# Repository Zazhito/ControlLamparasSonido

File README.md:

# ControlLamparasSonido
 Controlador de intensidad luminica utilizando sonido , Este proyecto fue extraido del libro "500 ELECTRONIC PROJECTS" del autor ARSATH NATHEEM S

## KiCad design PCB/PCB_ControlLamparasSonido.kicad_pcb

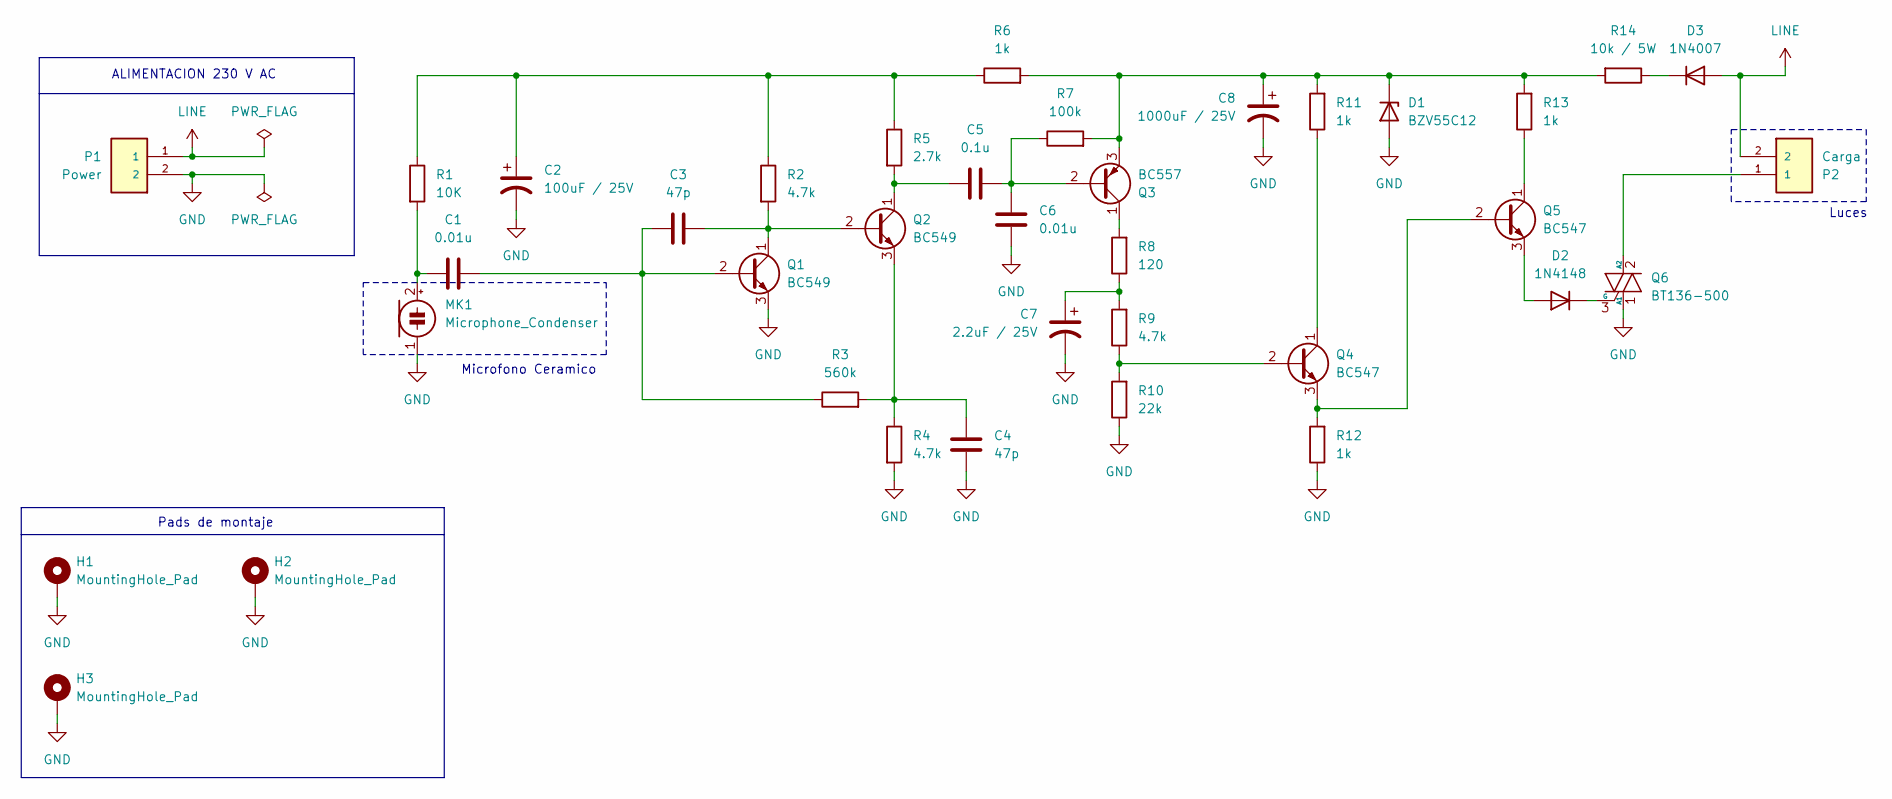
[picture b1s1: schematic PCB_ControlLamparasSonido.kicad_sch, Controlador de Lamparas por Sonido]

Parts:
C1, C6: 0.01u; C_0805_2012Metric
C2: 100uF / 25V; CP_Radial_D5.0mm_P2.00mm
C3, C4: 47p; C_0805_2012Metric
C5: 0.1u; C_0805_2012Metric
C7: 2.2uF / 25V; C_1206_3216Metric
C8: 1000uF / 25V; CP_Radial_D10.0mm_P2.50mm
D1: BZV55C12; D_MiniMELF
D2: 1N4148; D_DO-35_SOD27_P7.62mm_Horizontal
D3: 1N4007; D_DO-41_SOD81_P10.16mm_Horizontal
H1, H2, H3: MountingHole_Pad; MountingHole_2.2mm_M2_ISO7380_Pad
MK1: Microphone_Condenser; MIC_CMA-4544PF-W
P1: Power; TE_282837-2; PARTREV G3
P2: Carga; TE_282837-2; PARTREV G3
Q1, Q2: BC549; TO-92_Inline
Q3: BC557; TO-92_Inline
Q4, Q5: BC547; TO-92_Inline
Q6: BT136-500; TO-220-3_Vertical
R1: 10K; R_0805_2012Metric
R2, R4, R9: 4.7k; R_0805_2012Metric
R3: 560k; R_0805_2012Metric
R5: 2.7k; R_0805_2012Metric
R6, R11, R12, R13: 1k; R_0805_2012Metric
R7: 100k; R_0805_2012Metric
R8: 120; R_0805_2012Metric
R10: 22k; R_0805_2012Metric
R14: 10k / 5W; R_Axial_Power_L20.0mm_W6.4mm_P22.40mm

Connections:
GND: C2.2, C4.1, C6.1, C7.2, C8.2, D1.2 (A), H1.1, H2.1, H3.1, MK1.1 (-), P1.2, Q1.3 (E), Q6.1 (A1), R4.2, R10.1, R12.1
LINE: D3.2 (A), P1.1, P2.2
unnamed: C2.1, R1.1, R2.1, R5.1, R6.1
unnamed: C7.1, R8.1, R9.2
unnamed: C8.1, D1.1 (K), Q3.3 (E), R6.2, R7.2, R11.2, R13.2, R14.2
unnamed: D2.2 (A), Q5.3 (E)
unnamed: D2.1 (K), Q6.3 (G)
unnamed: D3.1 (K), R14.1
unnamed: C1.1, MK1.2 (+), R1.2
unnamed: C1.2, C3.1, Q1.2 (B), R3.1
unnamed: C3.2, Q1.1 (C), Q2.2 (B), R2.2
unnamed: C5.1, Q2.1 (C), R5.2
unnamed: C4.2, Q2.3 (E), R3.2, R4.1
unnamed: C5.2, C6.2, Q3.2 (B), R7.1
unnamed: Q3.1 (C), R8.2
unnamed: Q4.2 (B), R9.1, R10.2
unnamed: Q4.1 (C), R11.1
unnamed: Q4.3 (E), Q5.2 (B), R12.2
unnamed: Q5.1 (C), R13.1
unnamed: P2.1, Q6.2 (A2)

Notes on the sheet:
ALIMENTACION 230 V AC
Luces
Microfono Ceramico
Pads de montaje

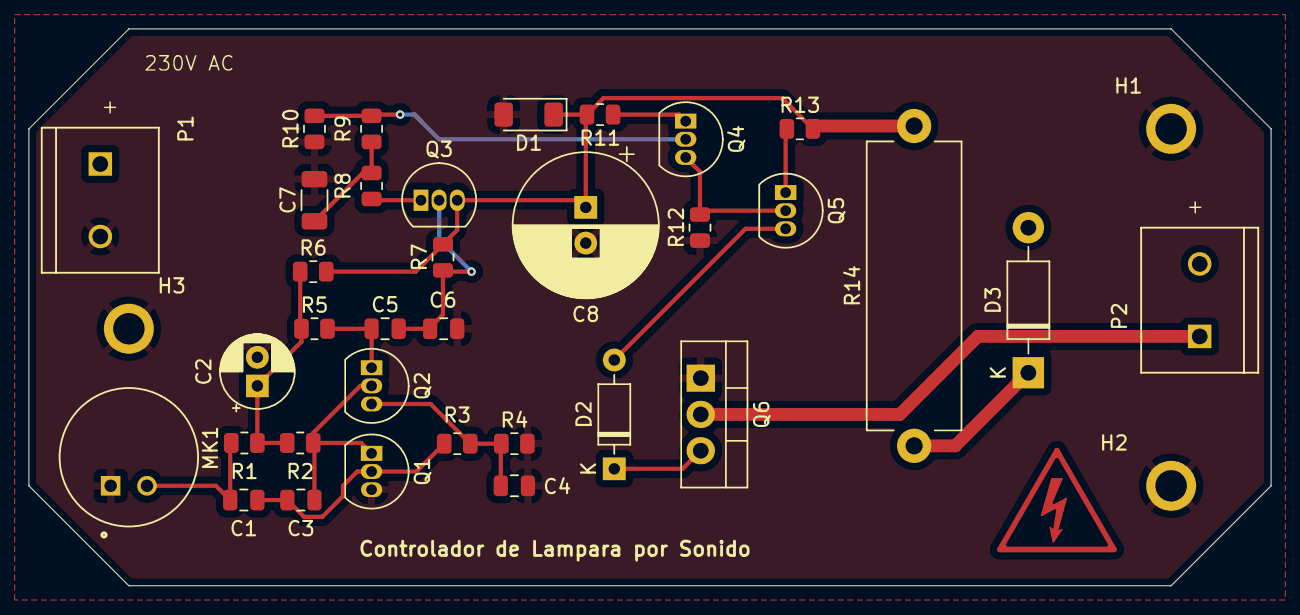
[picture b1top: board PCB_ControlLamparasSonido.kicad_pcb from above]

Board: 2 copper layers, 87.0 x 39.0 mm, 37 parts (0 on the bottom side), 20 nets.

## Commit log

2025-04-17 SimulacionSPICE
    Simulaciones en LTSPICE
2025-04-18 Biblioteca TRIAC
    Se añadio la biblioteca del TRIAC para completar el diseño
2025-04-18 EsquemaPCB
    Se añadio el esquematico de la PCB
2025-04-18 PCB
    Diseño terminado de la PCB 2 capas
2025-04-21 Finalizado
    Proyecto Finalizado
